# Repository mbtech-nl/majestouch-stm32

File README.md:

# majestouch-stm32

A drop-in replacement controller for the full-size Filco Majestouch, built
around an STM32F072. It replaces the stock daughterboard, plugs into the same
36-pin header on the main PCB and runs [QMK](https://qmk.fm); the QMK keyboard
definition is included.

**Download:** the [latest release](https://github.com/mbtech-nl/majestouch-stm32/releases/latest)
has everything needed to build the controller: the Gerber package to order the board from
any PCB fab, the parts list (BOM) and the ready-built QMK firmware (`.bin`).
See [Making one](#making-one) for how to order, assemble and flash it.

<p align="center"><sub>Component side (faces the main PCB) and outward side, rendered from the KiCad board.</sub></p>

## Background

My 2010 Majestouch was getting on, so I went looking for a replacement.
Nothing on offer today quite suited my taste, and every switch still worked.
Maybe a good clean and a fresh set of keycaps would hold me over for the next
15 years?

Still, all those modern keyboards did NKRO over USB, and that reminded me:
mine used to do NKRO too, back when it was plugged in over PS/2. PS/2 left my
desk a long time ago, and over USB the stock controller only does 6KRO.
Reading up on it, I came across the [Kitten Paw](https://deskthority.net/wiki/Costar_replacement_controllers)
(ATmega32U2 + 74HC154), the replacement controller for Costar boards such as
the Filco, about a decade after everyone else did. I also found
[Majestouch-2-TKL-Replacement-Controller](https://github.com/calliah333/Majestouch-2-TKL-Replacement-Controller),
which does the same for the Majestouch 2 TKL with an STM32.

So I designed my own replacement controller, taking that STM32 approach to
the full-size board. It's my first open source hardware project, and the
design turned out to be quite straightforward. Did I need NKRO? Honestly, I
never noticed it was missing. Am I happy with the result? Definitely.

The board keeps it simple:

- **STM32F072CBT6**: crystal-less USB (HSI48 + clock recovery), internal
  flash, ROM bootloader with USB DFU, and 5 V-tolerant pins for the lock LEDs.
  All 26 matrix lines are scanned directly, with no decoder chip.
- **NKRO over USB** (on by default in the QMK definition), where the stock
  controller only did 6KRO over USB.
- **16 components**, LQFP-48 and 0603/0805 passives: hand-solderable.
- USB ESD protection (USBLC6-2SC6) and a 3.3 V LDO (AP2112K-3.3).
- 50 × 18 mm, 2 layers, standard process at any PCB fab.

## Compatibility

Built for and measured on a full-size ANSI Majestouch with main PCB
`CST 104/5/6 Main PCBA Rev 1.2` and stock daughterboard
`CST-DAUGHTER PCBA Rev 3.1 ESD`.

The full-size Filcos below share the same 36-pin header and matrix according
to deskthority, and the Kitten Paw is listed for the same main PCBs, so they
are expected to work, but are untested with this board:

| Keyboard | Main PCB |
|---|---|
| Majestouch (FKBN104/105) | CST-FKB/N-104/5/6 Main PCBA Rev 1.0 / 1.2 (2010) |
| Majestouch Linear R | CST-F104/5/6/8 Main PCB Rev 2.1 (2010) |
| Majestouch 2 | CST-F104/5/6/8 Main PCB Rev 3.0 (2012) |

Full NKRO needs a diode per key. Filco marks those boards with an N in the
model code (FKB**N**…, "N-key rollover using separate diodes"); the cheaper
2KRO models without it work too, but ghost on some key combinations.

Compare your stock controller with the pinout below before fitting. The QMK
definition has the ANSI layout; ISO boards work electrically, but the two
extra ISO keys need a layout of your own. The Majestouch TKL uses a different
header and does not fit.

## Repository

```
kicad/                       KiCad 9 project (schematic, board, design rules)
firmware/majestouch_stm32/   QMK keyboard definition
tools/check.py               validation: schematic, firmware pins and board
tools/fab.py                 fabrication package (Gerbers, drill, BOM)
docs/                        board renders, photos of the stock controller
```

`tools/check.py` checks the schematic against the STM32 datasheet pinout and
the Filco header map, checks that every pin in the QMK definition lands on the
right net, and runs KiCad's design rule check on the board. It needs KiCad 9
(`kicad-cli` and the `pcbnew` Python module).

## Header pinout

From the Filco Majestouch table on deskthority's
[controller matrix traces](https://deskthority.net/wiki/Controller_matrix_traces)
page, cross-checked pin for pin against the
[Kitten Paw schematic](https://deskthority.net/wiki/File:Kitten_Paw_20160418_Schematic.svg).
The component side
faces the main PCB; seen from that side, pin 1 is top-right, pins 1–18 run
right to left, and pin 19 sits directly below pin 1.

| Pin | Signal | STM32 | | Pin | Signal | STM32 |
|---|---|---|---|---|---|---|
| 1 | COL0 | PA5 | | 19 | ROW_K | PA3 |
| 2 | ROW_A | PA6 | | 20 | COL1 | PA2 |
| 3 | ROW_B | PA7 | | 21 | ROW_L | PA1 |
| 4 | ROW_C | PB0 | | 22 | COL2 | PA0 |
| 5 | ROW_D | PB1 | | 23 | COL3 | PF1 |
| 6 | ROW_E | PB2 | | 24 | ROW_M | PF0 |
| 7 | ROW_F | PB10 | | 25 | ROW_N | PC15 |
| 8 | ROW_G | PB11 | | 26 | ROW_O | PC14 |
| 9 | ROW_H | PB12 | | 27 | ROW_P | PC13 |
| 10 | ROW_I | PB13 | | 28 | ROW_Q | PB9 |
| 11 | ROW_J | PB14 | | 29 | COL4 | PB8 |
| 12 | GND | | | 30 | ROW_R | PB7 |
| 13 | USB D+ | ESD → PA12 | | 31 | COL5 | PB6 |
| 14 | USB D− | ESD → PA11 | | 32 | COL6 | PB5 |
| 15 | n/c | | | 33 | COL7 | PB4 |
| 16 | n/c | | | 34 | LED Num Lock | PB3 |
| 17 | n/c | | | 35 | LED Caps Lock | PA15 |
| 18 | VBUS | LDO in | | 36 | LED Scroll Lock | PA14 |

Pins 15 and 16 are tied to GND on the main PCB; this board leaves 15–17
unconnected.

<p align="center"><sub>The stock controller this board replaces: installed, solder side up, next to the lock LEDs and the USB cable connector; and removed, component side, oriented like the render above (CON2 = pins 1–18 on top, pin 1 at the right).</sub></p>

## Circuit

- **USB**: D+/D− pass through the USBLC6-2SC6 flow-through (in on pins 1/3,
  out on 6/4), so no route bypasses the clamp. The STM32's internal pull-up
  handles D+.
- **Power**: VBUS → AP2112K-3.3. Each MCU supply pin has its own decoupling
  cap: 1 µF + 10 nF on VDDA, 100 nF on VDD, VDDIO2 and VBAT.
- **Matrix**: 18 rows driven, 8 columns read (QMK `COL2ROW`). The main PCB
  has no pull-ups to 5 V on the matrix lines, so the 3.6 V-only pins
  (PA0–PA7, PB0/PB1) are safe.
- **Lock LEDs**: the LED anodes sit on +5 V on the main PCB. The MCU sinks
  each LED through a 10 k resistor from a 5 V-tolerant pin in open-drain mode,
  like the stock controller (~0.3 mA).
- **BOOT / RESET**: 2.54 mm jumper holes. BOOT0 has a 10 k pull-down, NRST
  100 nF to GND.

**Board:** 50 × 18 mm, 2 layers, 1.2 mm FR-4. 0.15 mm tracks and clearance
(0.25 mm for power), 0.3 mm vias, GND pour on both sides. The MCU sits at 45°
so each side fans out to one header row. ICs, C1 and the LED resistors are on
the component side (facing the main PCB), the other passives on the outward
side. The outward side carries the reference designators, BOOT/RST labels and
a QR code linking to this repository.

## Making one

### Board

```sh
cd tools
python3 check.py   # validate first
python3 fab.py
```

This builds `kicad/fab/majestouch_stm32-gerbers-<rev>.zip` (Gerbers and drill
files, accepted by any PCB fab) plus `bom.csv` with the parts used and what an
equivalent needs. Tagged releases have both attached, together with the QMK
firmware, built and validated by GitHub Actions
(`.github/workflows/release.yml`).

Order settings: 2 layers, FR-4, 1.2 mm (the stock board's thickness; 1.6 mm
fits too), HASL lead-free or ENIG. The design stays within standard rules
(0.15 mm track/space, 0.3 mm drills). If your fab prints an order number on
the board (JLCPCB does by default), choose the option without it, so it
doesn't land on the QR code. `cpl.csv` (pick-and-place) is only needed if the
fab assembles the board.

### Parts

| Ref | Part | Package |
|---|---|---|
| U1 | STM32F072CBT6 | LQFP-48 |
| U2 | AP2112K-3.3 | SOT-23-5 |
| U3 | USBLC6-2SC6 | SOT-23-6 |
| C1 | 4.7 µF | 0805 |
| C2 | 10 µF | 0805 |
| C3–C6, C9 | 100 nF | 0603 |
| C7 | 1 µF | 0603 |
| C8 | 10 nF | 0603 |
| R1–R4 | 10 k | 0603 |
| J1, J2 | 2.0 mm pin header, 1 × 40 strip snapped to 2 × 18 | |
| J3, J4 | 2.54 mm 1 × 2 header (optional) | |

Any equivalent part works: X5R/X7R capacitors at 10 V or more, 1 % or 5 %
resistors.

### Assembly

U1, U2, U3, C1 and R2–R4 go on the component side, the other passives on the
back; every part is labelled on the silkscreen. Mind the pin-1 triangles on
U1, U2 and U3: U2 and U3 short VBUS to GND when rotated. Solder the pin
headers last, with the plastic on the component side, then fit the board in
place of the stock controller.

### Firmware

Each release has a ready-built `majestouch_stm32-qmk-<version>.bin` with the
default keymap; the release notes name the QMK version it was built with. To
build it yourself, copy `firmware/majestouch_stm32` into
`qmk_firmware/keyboards/`, then:

```sh
qmk compile -kb majestouch_stm32 -km default
```

First flash: bridge the BOOT jumper while plugging in USB (or bridge BOOT and
tap RESET) to start the STM32's DFU bootloader, then
`qmk flash -kb majestouch_stm32 -km default`, or for the release binary
`dfu-util -a 0 -d 0483:df11 -s 0x08000000:leave -D majestouch_stm32-qmk-<version>.bin`.
After that, hold Esc while plugging in to get back to the bootloader.

The default keymap is a standard full-size ANSI layout. The Caps/Num/Scroll
LEDs follow the host's lock state.

## Verified on the keyboard

Measured on the target keyboard before ordering:

- outline and header position match the stock board (1:1 print);
- no connection from VBUS to any matrix pin on the main PCB;
- lock LED anodes on +5 V, active low;
- enough height between the boards; stock board 1.2 mm thick.

Tested with the first board built from these files, in the same keyboard:

- every key registers, including many keys at once (NKRO);
- Num/Caps/Scroll LEDs follow the host's lock state;
- first flash over BOOT + RST, later ones by holding Esc while plugging in.

<p align="center"><sub>The first board: assembled, installed in place of the stock controller (oriented like the photo of the stock one above), and next to the stock controller it replaces. Forgive the prototype-quality soldering.</sub></p>

## References

- [Controller matrix traces](https://deskthority.net/wiki/Controller_matrix_traces)
  (deskthority wiki): the Filco Majestouch header pinout and matrix.
- [Kitten Paw schematic](https://deskthority.net/wiki/File:Kitten_Paw_20160418_Schematic.svg)
  by Bpiphany (public domain): the reference replacement controller for the
  full-size Filco, used to cross-check the header.
- [Costar replacement controllers](https://deskthority.net/wiki/Costar_replacement_controllers)
  (deskthority wiki): the Kitten Paw and its relatives.
- [Majestouch-2-TKL-Replacement-Controller](https://github.com/calliah333/Majestouch-2-TKL-Replacement-Controller):
  an STM32 replacement controller for the Majestouch 2 TKL.
- [STM32F072CB datasheet](https://www.st.com/resource/en/datasheet/stm32f072cb.pdf) (DS9826),
  [USBLC6-2 datasheet](https://www.st.com/resource/en/datasheet/usblc6-2.pdf),
  [AP2112 datasheet](https://www.diodes.com/assets/Datasheets/AP2112.pdf).

## License

MIT, see [LICENSE](LICENSE). This covers the hardware, the tools and the QMK
keyboard definition. Firmware built with QMK includes QMK itself, which is
GPL-2.0-or-later, so compiled binaries fall under the GPL.

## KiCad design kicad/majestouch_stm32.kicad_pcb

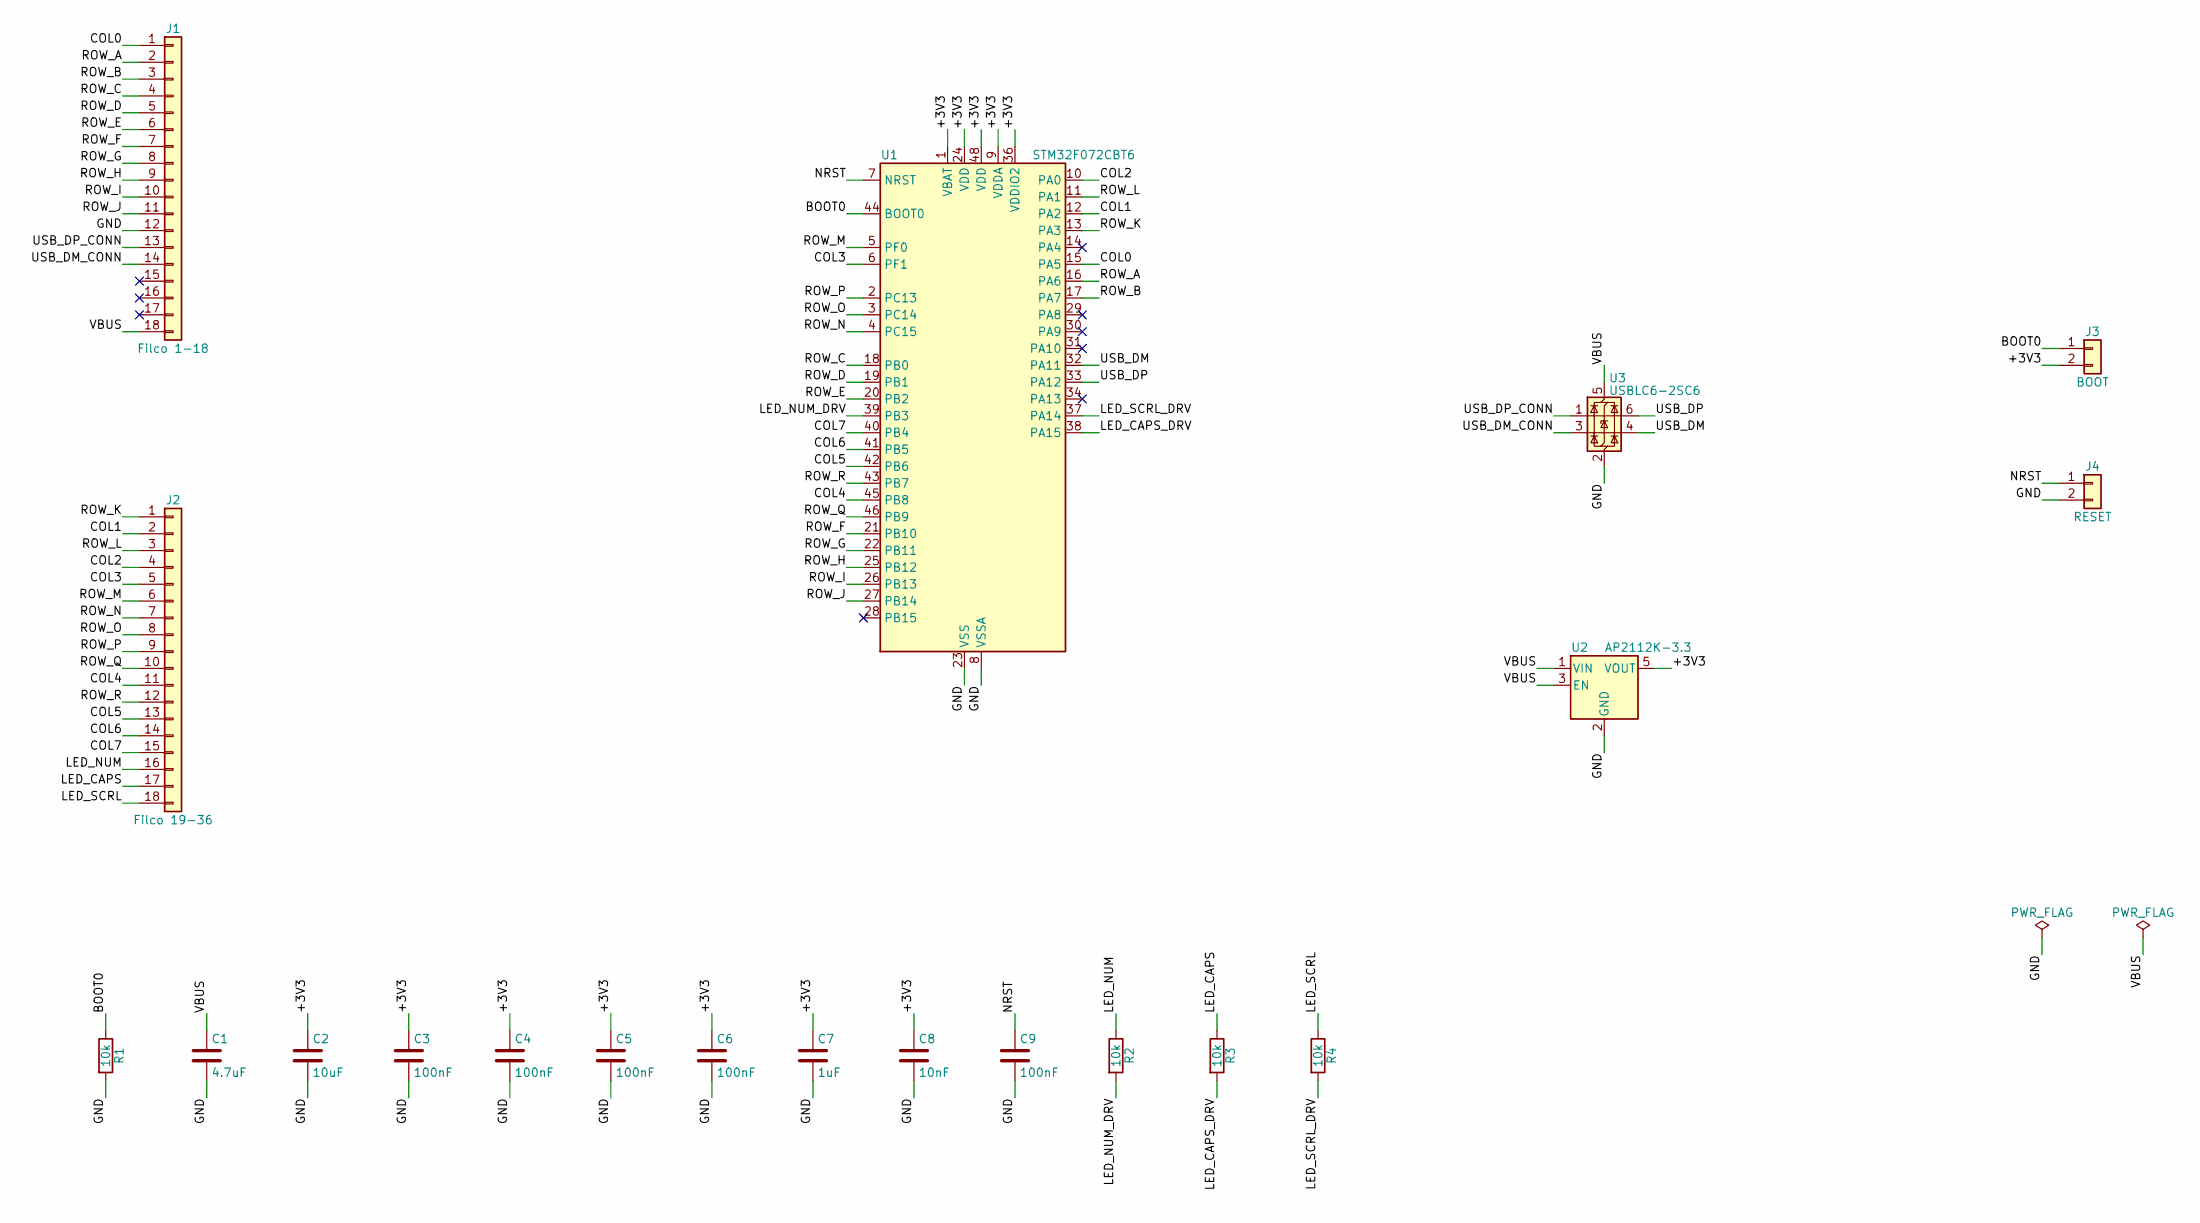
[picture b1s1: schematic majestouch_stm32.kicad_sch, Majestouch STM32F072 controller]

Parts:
C1: 4.7uF; C_0805_2012Metric
C2: 10uF; C_0805_2012Metric
C3, C4, C5, C6, C9: 100nF; C_0603_1608Metric
C7: 1uF; C_0603_1608Metric
C8: 10nF; C_0603_1608Metric
J1: Filco 1-18; PinHeader_1x18_P2.00mm_Vertical
J2: Filco 19-36; PinHeader_1x18_P2.00mm_Vertical
J3: BOOT; PinHeader_1x02_P2.54mm_Vertical
J4: RESET; PinHeader_1x02_P2.54mm_Vertical
R1, R2, R3, R4: 10k; R_0603_1608Metric
U1: STM32F072CBT6; LQFP-48_7x7mm_P0.5mm
U2: AP2112K-3.3; SOT-23-5
U3: USBLC6-2SC6; SOT-23-6

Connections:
/+3V3: C2.1, C3.1, C4.1, C5.1, C6.1, C7.1, C8.1, J3.2, U1.1 (VBAT), U1.9 (VDDA), U1.24 (VDD), U1.36 (VDDIO2), U1.48 (VDD), U2.5 (VOUT)
/BOOT0: J3.1, R1.1, U1.44 (BOOT0)
/COL0: J1.1, U1.15 (PA5)
/COL1: J2.2, U1.12 (PA2)
/COL2: J2.4, U1.10 (PA0)
/COL3: J2.5, U1.6 (PF1)
/COL4: J2.11, U1.45 (PB8)
/COL5: J2.13, U1.42 (PB6)
/COL6: J2.14, U1.41 (PB5)
/COL7: J2.15, U1.40 (PB4)
/GND: C1.2, C2.2, C3.2, C4.2, C5.2, C6.2, C7.2, C8.2, C9.2, J1.12, J4.2, R1.2, U1.8 (VSSA), U1.23 (VSS), U1.35 (VSS), U1.47 (VSS), U2.2 (GND), U3.2 (GND)
/LED_CAPS: J2.17, R3.1
/LED_CAPS_DRV: R3.2, U1.38 (PA15)
/LED_NUM: J2.16, R2.1
/LED_NUM_DRV: R2.2, U1.39 (PB3)
/LED_SCRL: J2.18, R4.1
/LED_SCRL_DRV: R4.2, U1.37 (PA14)
/NRST: C9.1, J4.1, U1.7 (NRST)
/ROW_A: J1.2, U1.16 (PA6)
/ROW_B: J1.3, U1.17 (PA7)
/ROW_C: J1.4, U1.18 (PB0)
/ROW_D: J1.5, U1.19 (PB1)
/ROW_E: J1.6, U1.20 (PB2)
/ROW_F: J1.7, U1.21 (PB10)
/ROW_G: J1.8, U1.22 (PB11)
/ROW_H: J1.9, U1.25 (PB12)
/ROW_I: J1.10, U1.26 (PB13)
/ROW_J: J1.11, U1.27 (PB14)
/ROW_K: J2.1, U1.13 (PA3)
/ROW_L: J2.3, U1.11 (PA1)
/ROW_M: J2.6, U1.5 (PF0)
/ROW_N: J2.7, U1.4 (PC15)
/ROW_O: J2.8, U1.3 (PC14)
/ROW_P: J2.9, U1.2 (PC13)
/ROW_Q: J2.10, U1.46 (PB9)
/ROW_R: J2.12, U1.43 (PB7)
/USB_DM: U1.32 (PA11), U3.4 (I/O2)
/USB_DM_CONN: J1.14, U3.3 (I/O2)
/USB_DP: U1.33 (PA12), U3.6 (I/O1)
/USB_DP_CONN: J1.13, U3.1 (I/O1)
/VBUS: C1.1, J1.18, U2.1 (VIN), U2.3 (EN), U3.5 (VBUS)

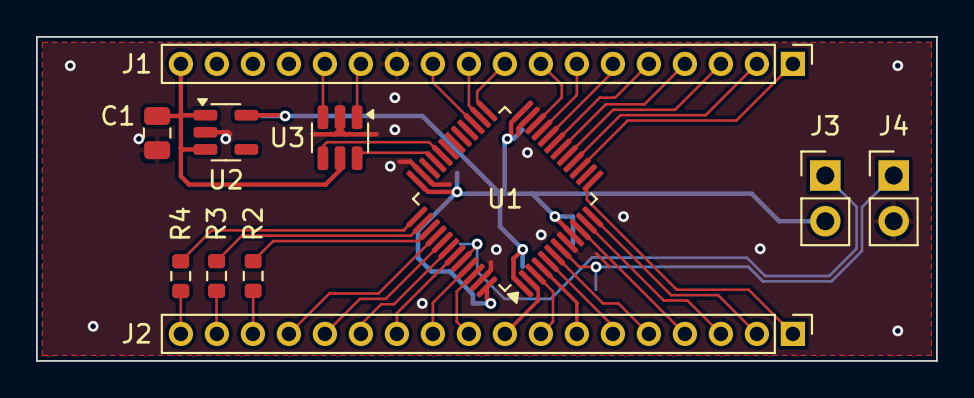
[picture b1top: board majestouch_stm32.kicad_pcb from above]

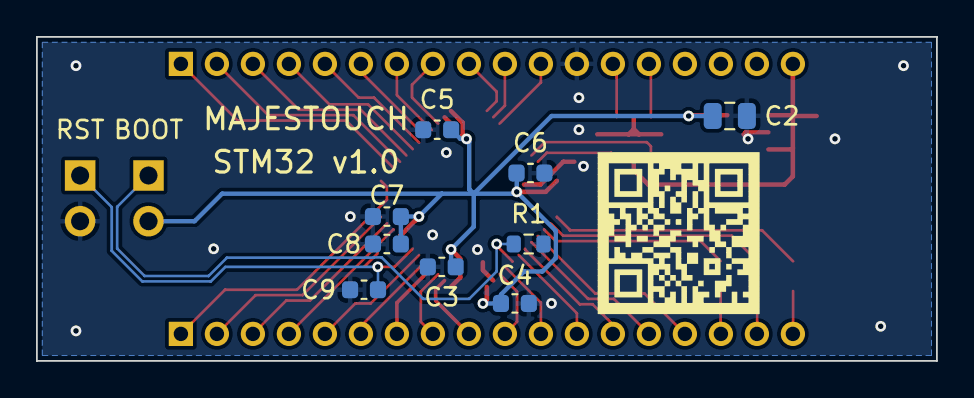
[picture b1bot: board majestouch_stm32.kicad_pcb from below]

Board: 2 copper layers, 50.0 x 18.0 mm, 20 parts (9 on the bottom side), 41 nets.

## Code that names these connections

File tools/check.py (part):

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
# STM32F072 LQFP-48 pinout (DS9826) and its 5 V-tolerant (FT) pins in use here
STM32_PIN = {name: i + 1 for i, name in enumerate(
    'VBAT PC13 PC14 PC15 PF0 PF1 NRST VSSA VDDA PA0 PA1 PA2 PA3 PA4 PA5 PA6 PA7 PB0 PB1 '
    'PB2 PB10 PB11 VSS VDD PB12 PB13 PB14 PB15 PA8 PA9 PA10 PA11 PA12 PA13 VSS VDDIO2 '
    'PA14 PA15 PB3 PB4 PB5 PB6 PB7 BOOT0 PB8 PB9 VSS VDD'.split())}
STM32_NAME = {str(n): name for name, n in STM32_PIN.items()}   # VSS/VDD repeat: checked by number
STM32_FT = {'PA8', 'PA9', 'PA10', 'PA13', 'PA14', 'PA15', 'PB3', 'PB4', 'PB5', 'PB6', 'PB7',
            'PB8', 'PB9'}

errors = []

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            error(f'{net}: expected header + U1 only, got {sorted(nets.get(net, ()))}')
            continue
        pin = next(p for r, p in nets[net] if r == 'U1')
        if not STM32_NAME.get(pin, '').startswith('P') or STM32_NAME[pin] in ('PA11', 'PA12'):
            error(f'{net}: on U1 pin {pin} ({STM32_NAME.get(pin)}), not a free GPIO')

    # lock LEDs: header pin -> series resistor -> 5 V-tolerant MCU pin
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    expect('U3', 1, 'USB_DP_CONN'); expect('U3', 6, 'USB_DP')
    expect('U3', 3, 'USB_DM_CONN'); expect('U3', 4, 'USB_DM')
    expect('U3', 2, 'GND'); expect('U3', 5, 'VBUS')
    expect('U1', STM32_PIN['PA12'], 'USB_DP'); expect('U1', STM32_PIN['PA11'], 'USB_DM')
    for net, want in (('USB_DP_CONN', ['J1', 'U3']), ('USB_DM_CONN', ['J1', 'U3']),
                      ('USB_DP', ['U1', 'U3']), ('USB_DM', ['U1', 'U3'])):
        if refs(net) != want:
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
# --- 2. firmware ------------------------------------------------------------------
def check_firmware(pin_net):
    def net_of(qmk_pin):                    # QMK "A6" -> PA6 -> U1 pin -> net
        n = STM32_PIN.get('P' + qmk_pin)
        return pin_net.get(('U1', str(n))) if n else None

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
